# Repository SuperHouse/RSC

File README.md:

Relay Shield Carrier
====================

Copyright 2019 SuperHouse Automation Pty Ltd  www.superhouse.tv  

Mounting board for up to 4 Freetronics Relay Driver Shields.

Features:

 * I2C and power broken out to pin headers
 * Grove header
 * Qwiic header

More information is available at:

  http://www.superhouse.tv/rsc

INSTALLATION
------------
The design is saved as an EAGLE project. EAGLE PCB design software is
available from www.cadsoftusa.com free for non-commercial use. To use
this project download it and place the directory containing these files
into the "eagle" directory on your computer.

DISTRIBUTION
------------
The specific terms of distribution of this project are governed by the
license referenced below.

LICENSE
-------
Licensed under the TAPR Open Hardware License (www.tapr.org/OHL).
The "license" folder within this repository also contains a copy of
this license in plain text format.

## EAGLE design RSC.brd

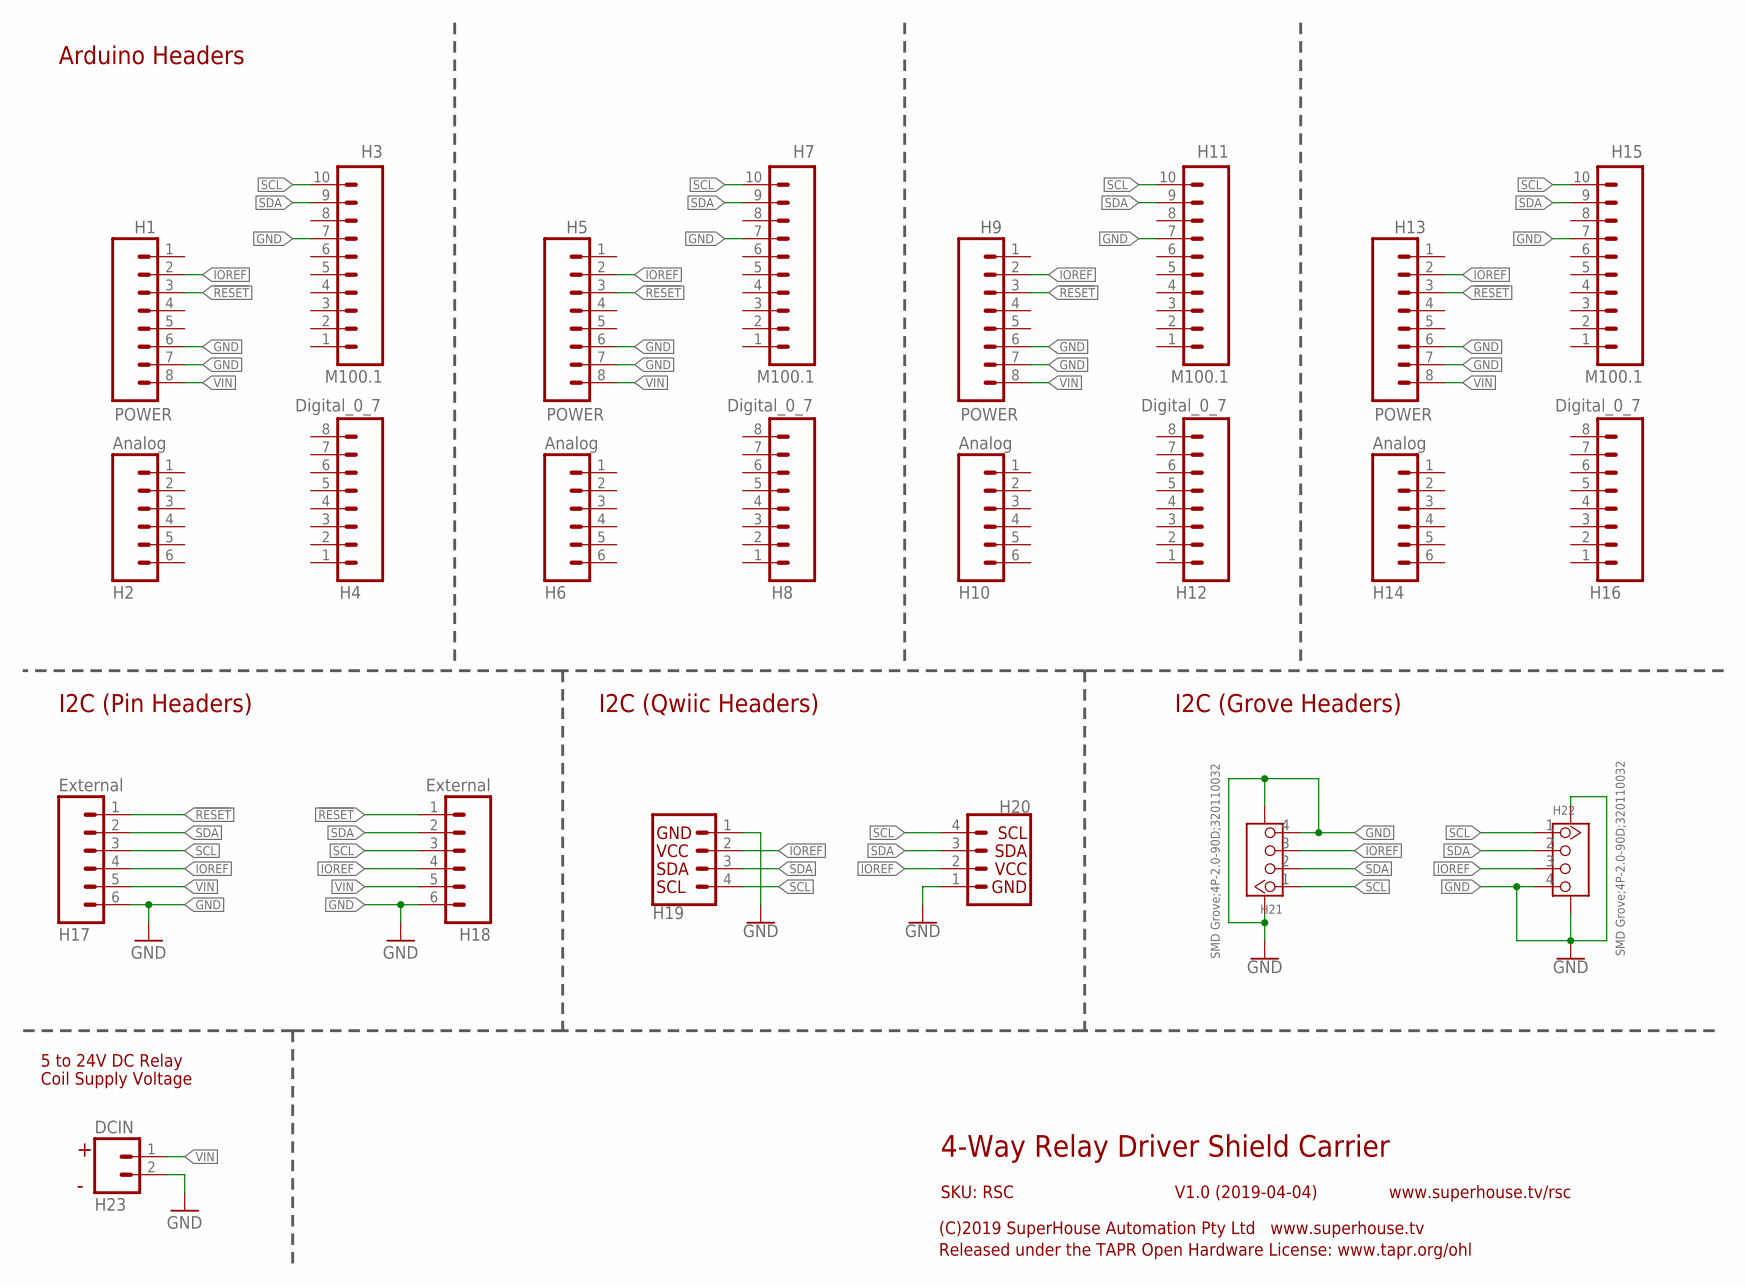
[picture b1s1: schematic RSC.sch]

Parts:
H1, H5, H9, H13: POWER; 1X08
H2, H6, H10, H14: Analog; 1X06
H3, H7, H11, H15: M100.1; 1X10
H4, H8, H12, H16: Digital_0_7; 1X08
H17, H18: External; 1X06
H19, H20: QWIIC_CONNECTORJS-1MM; 1X04_1MM_RA
H21, H22: SMD Grove;4P-2.0-90D;320110032; HW4-SMD-2.0-90D
H23: DCIN; SCREWTERMINAL-3.5MM-2

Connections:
!RESET: H1.3, H5.3, H9.3, H13.3, H17.1, H18.1
GND: H1.6, H1.7, H3.7, H5.6, H5.7, H7.7, H9.6, H9.7, H11.7, H13.6, H13.7, H15.7, H17.6, H18.6, H19.1, H20.1, H21.4, H21.SS1, H21.SS2, H22.4, H22.SS1, H22.SS2, H23.2
IOREF: H1.2, H5.2, H9.2, H13.2, H17.4, H18.4, H19.2, H20.2, H21.3, H22.3
SCL: H3.10, H7.10, H11.10, H15.10, H17.3, H18.3, H19.4, H20.4, H21.1, H22.1
SDA: H3.9, H7.9, H11.9, H15.9, H17.2, H18.2, H19.3, H20.3, H21.2, H22.2
VIN: H1.8, H5.8, H9.8, H13.8, H17.5, H18.5, H23.1

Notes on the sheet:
4-Way Relay Driver Shield Carrier
V1.0 (2019-04-04)
SKU: RSC
Arduino Headers
(C)2019 SuperHouse Automation Pty Ltd www.superhouse.tv
Released under the TAPR Open Hardware License: www.tapr.org/ohl
www.superhouse.tv/rsc
I2C (Pin Headers)
I2C (Qwiic Headers)
I2C (Grove Headers)
Coil Supply Voltage
5 to 24V DC Relay

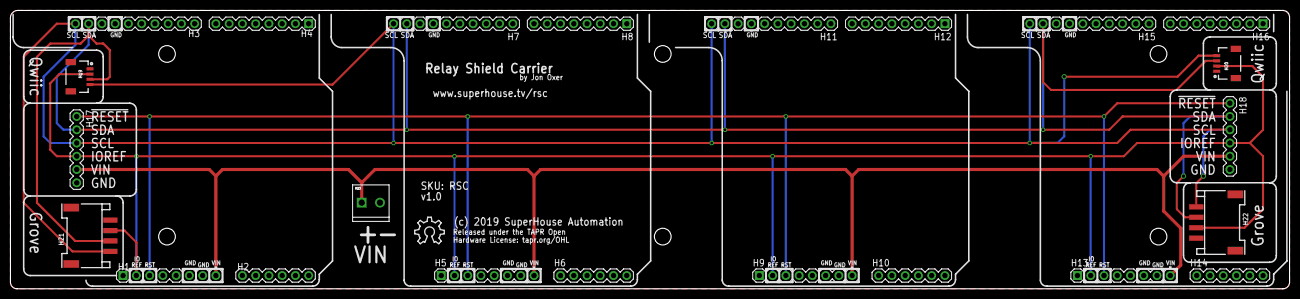
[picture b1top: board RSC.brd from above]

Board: 2 copper layers, 245.1 x 53.3 mm, 24 parts (0 on the bottom side), 6 nets.

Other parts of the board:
U$6: OSHW_10X200_NOTEXT

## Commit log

2019-03-18 Initial import of files from Relay8
2019-04-11 Layout for v1.0 release
2019-04-11 Renamed project files
2019-04-11 Added docs
2019-04-22 Changed designators to make them sequential
2019-09-03 Added mechanical dimensions
2021-03-11 Added PDF of schematic.

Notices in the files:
RSC.brd:
Hardware License: tapr.org/OHL
parts and their libraries:
SparkFun-Connectors: Licensing: Creative Commons ShareAlike 4.0 International - https://creativecommons.org/licenses/by-sa/4.0
